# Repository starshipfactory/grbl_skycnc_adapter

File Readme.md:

# GRBL SKYCNC Adapter

Für unsere Skycnc Maschine wollen wir einen neue Zeitgemässe Steuerungseinheit implementieren. Hier kann die Arduino basierte Steuerungssoftware grbl eingesetzt werden.

Für die nutzung von grbl mit der aktuell vorhandenen hardware sind folgende Schnittstellen auf einem interfaceboard zu designen:

- [x] Interface zu Schrittmotortreibern, Lieferung 5V und GND für Ansteuerung Optokoppler
- [x] Interface zu Tastkopf für Werkzeuglänge und Werkstückdetektion (GND -> Maschine, Sense -> Werkzeug)
- [x] Interface zu Spindelsteuerung mit Freigabe und 0-10V Drehzahlsteuerung
- [x] Interface zu bestehenden Endschaltern / Austausch der Endschalter
- [ ] Ersatz der Hardwareschalter durch neue
- [x] Vorbereitung für Anschluss Reset/Abort, FeedHold, CycleStart/Resume
- [ ] Einbau zusätzlicher Taster für Reset/Abort, FeedHold, CycleStart/Resume

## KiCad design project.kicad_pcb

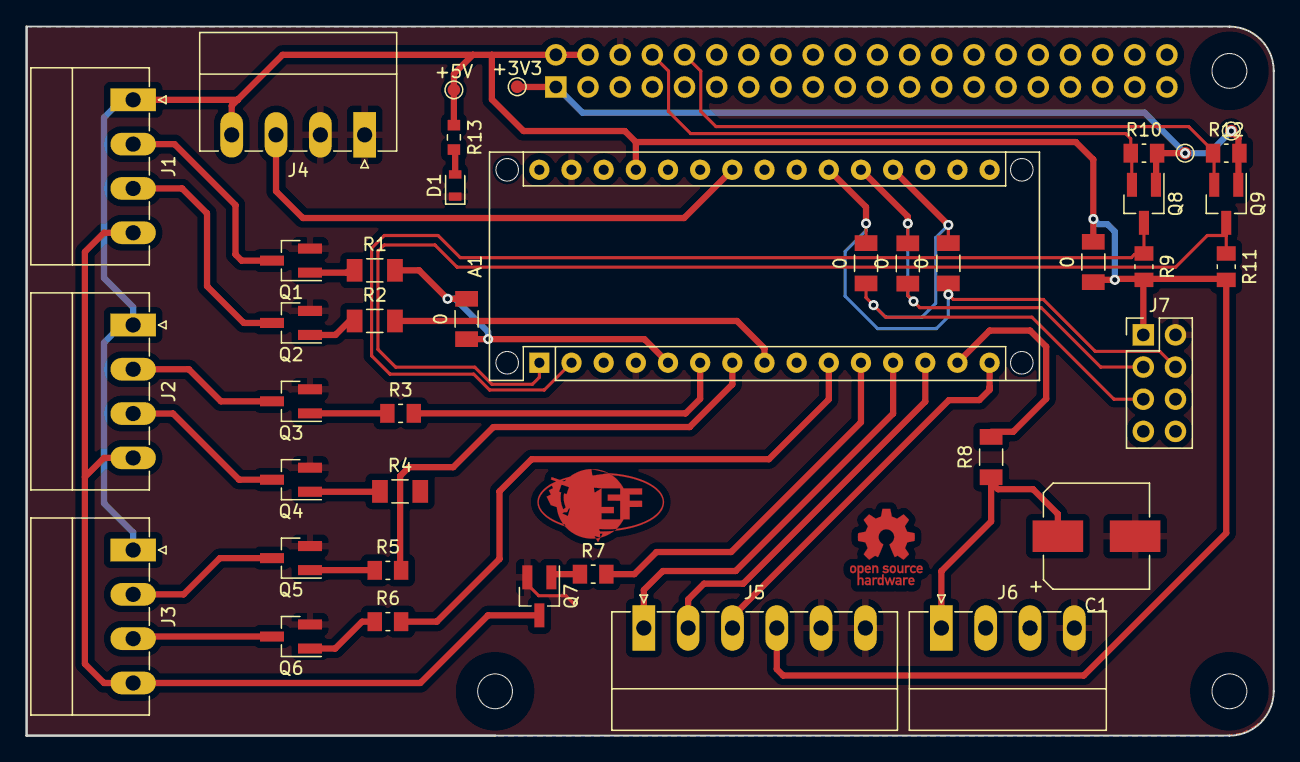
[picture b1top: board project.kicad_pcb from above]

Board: 2 copper layers, 98.5 x 56.0 mm, 43 parts (1 on the bottom side), 40 nets.

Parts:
0, 0#2, 0#3, 0#4, 0#5: 0; R_1206_3216Metric_Pad1.24x1.80mm_HandSolder
+3V3, +3V3#2: TestPoint_Pad_D1.0mm
+3V3#3: +3V3; TestPoint_Pad_D1.0mm
+5V: +5V; TestPoint_Pad_D1.0mm
A1: Arduino_Nano_v3.x; Arduino_Nano_WithMountingHoles
C1: 1uF; CP_Elec_8x10
D1: LED; D_0603_1608Metric_Pad0.67x1.00mm_HandSolder
J1, J2, J3, J4, J6: Conn_01x04; PhoenixContact_MC_1,5_4-G-3.5_1x04_P3.50mm_Horizontal
J5: Conn_01x06; PhoenixContact_MC_1,5_6-G-3.5_1x06_P3.50mm_Horizontal
J7: Conn_01x04; PinHeader_2x04_P2.54mm_Vertical
J9: Conn_02x20_Odd_Even; pi-gpio
Q1, Q2, Q3, Q4, Q5, Q6, Q7: BC848; SOT-23_Handsoldering
Q8, Q9: 2N7002; SOT-23_Handsoldering
R1, R2, R4: 10k; R_1206_3216Metric_Pad1.24x1.80mm_HandSolder
R3, R5, R6, R7, R9, R10, R11, R12: 10k; R_0805_2012Metric_Pad1.15x1.50mm_HandSolder
R8: 47k; R_1206_3216Metric_Pad1.24x1.80mm_HandSolder
R13: 220; R_0603_1608Metric_Pad0.84x1.00mm_HandSolder
Ref**: Val**; sf_logo

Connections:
+3V3: +3V3.1, +3V3#2.1, +3V3#3.1, J9.1, Q8.1 (G), Q9.1 (G), R10.2, R12.2
+5V: 0#2.1, 0#2.2, +5V.1, A1.27 (+5V), J1.1, J2.1, J3.1, J4.4, J5.4, J7.1, J9.2, J9.4, R9.2, R11.2, R13.1
/Stell_DZ: C1.1, J6.1, R8.1
CycleStart/Resume: 0#3.2, 0#5.1
CycleStart/Resume: A1.21 (A2), J7.4
DirX: A1.8 (D5), R2.2
DirXOut: J1.3, Q2.3 (C)
DirY: A1.9 (D6), R4.2
DirYOut: J2.3, Q4.3 (C)
DirZ: A1.10 (D7), R6.2
DirZOut: J3.3, Q6.3 (C)
Earth: A1.4 (GND), A1.29 (GND), C1.2, D1.1 (K), J4.1, J4.2, J5.5, J5.6, J6.4, J7.2, J9.6, Q1.2 (E), Q2.2 (E), Q3.2 (E), Q4.2 (E), Q5.2 (E), Q6.2 (E), Q7.2 (E)
FeedHold: 0#4.1, 0#4.2, A1.20 (A1), J7.3
LimitX: A1.12 (D9), J5.1
LimitY: A1.13 (D10), J5.2
LimitZ: A1.15 (D12), J5.3
unnamed: D1.2 (A), R13.2
unnamed: Q1.1 (B), R1.1
unnamed: Q2.1 (B), R2.1
unnamed: Q3.1 (B), R3.1
unnamed: Q4.1 (B), R4.1
unnamed: Q5.1 (B), R5.1
unnamed: Q6.1 (B), R6.1
unnamed: Q7.1 (B), R7.1
Probe: A1.24 (A5), J4.3
RXD: J9.10, Q9.2 (S), R12.1
RX_5V: A1.2 (D0/RX), Q8.3 (D), R9.1
Reset/Abort: 0#3.1, 0#5.2
Reset/Abort: A1.19 (A0), J7.5
SpindlePWM: A1.14 (D11), R8.2
StepX: 0.1, 0.2, A1.5 (D2), R1.2
StepXOut: J1.2, Q1.3 (C)
StepY: A1.6 (D3), R3.2
StepYOut: J2.2, Q3.3 (C)
StepZ: A1.7 (D4), R5.2
StepZOut: J3.2, Q5.3 (C)
StepperEN: A1.11 (D8), R7.2
StepperENOut: J1.4, J2.4, J3.4, Q7.3 (C)
TXD: J9.8, Q8.2 (S), R10.1
TX_5V: A1.1 (D1/TX), Q9.3 (D), R11.1

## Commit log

2017-12-08 Initiaier Commit
2017-12-08 Some improvements
2017-12-08 Fix Readme
2018-02-23 Diverse Anpassung, umstellug uf SMD
2018-02-27 Fertiggestelltes Layout
2018-03-02 Update auf vorhandene Bauteile & Korrektur 3D Objekte
2018-03-02 Neuerzeugen der Plots zum Ätzen
2024-06-11 Generated new Gerber files & new Kicad version
2024-06-11 Fixed wrong Layer on Gerbers
2024-06-11 Gerber 0 Positions are appreciated
2024-06-11 Set 0 for Gerbers for real this time
